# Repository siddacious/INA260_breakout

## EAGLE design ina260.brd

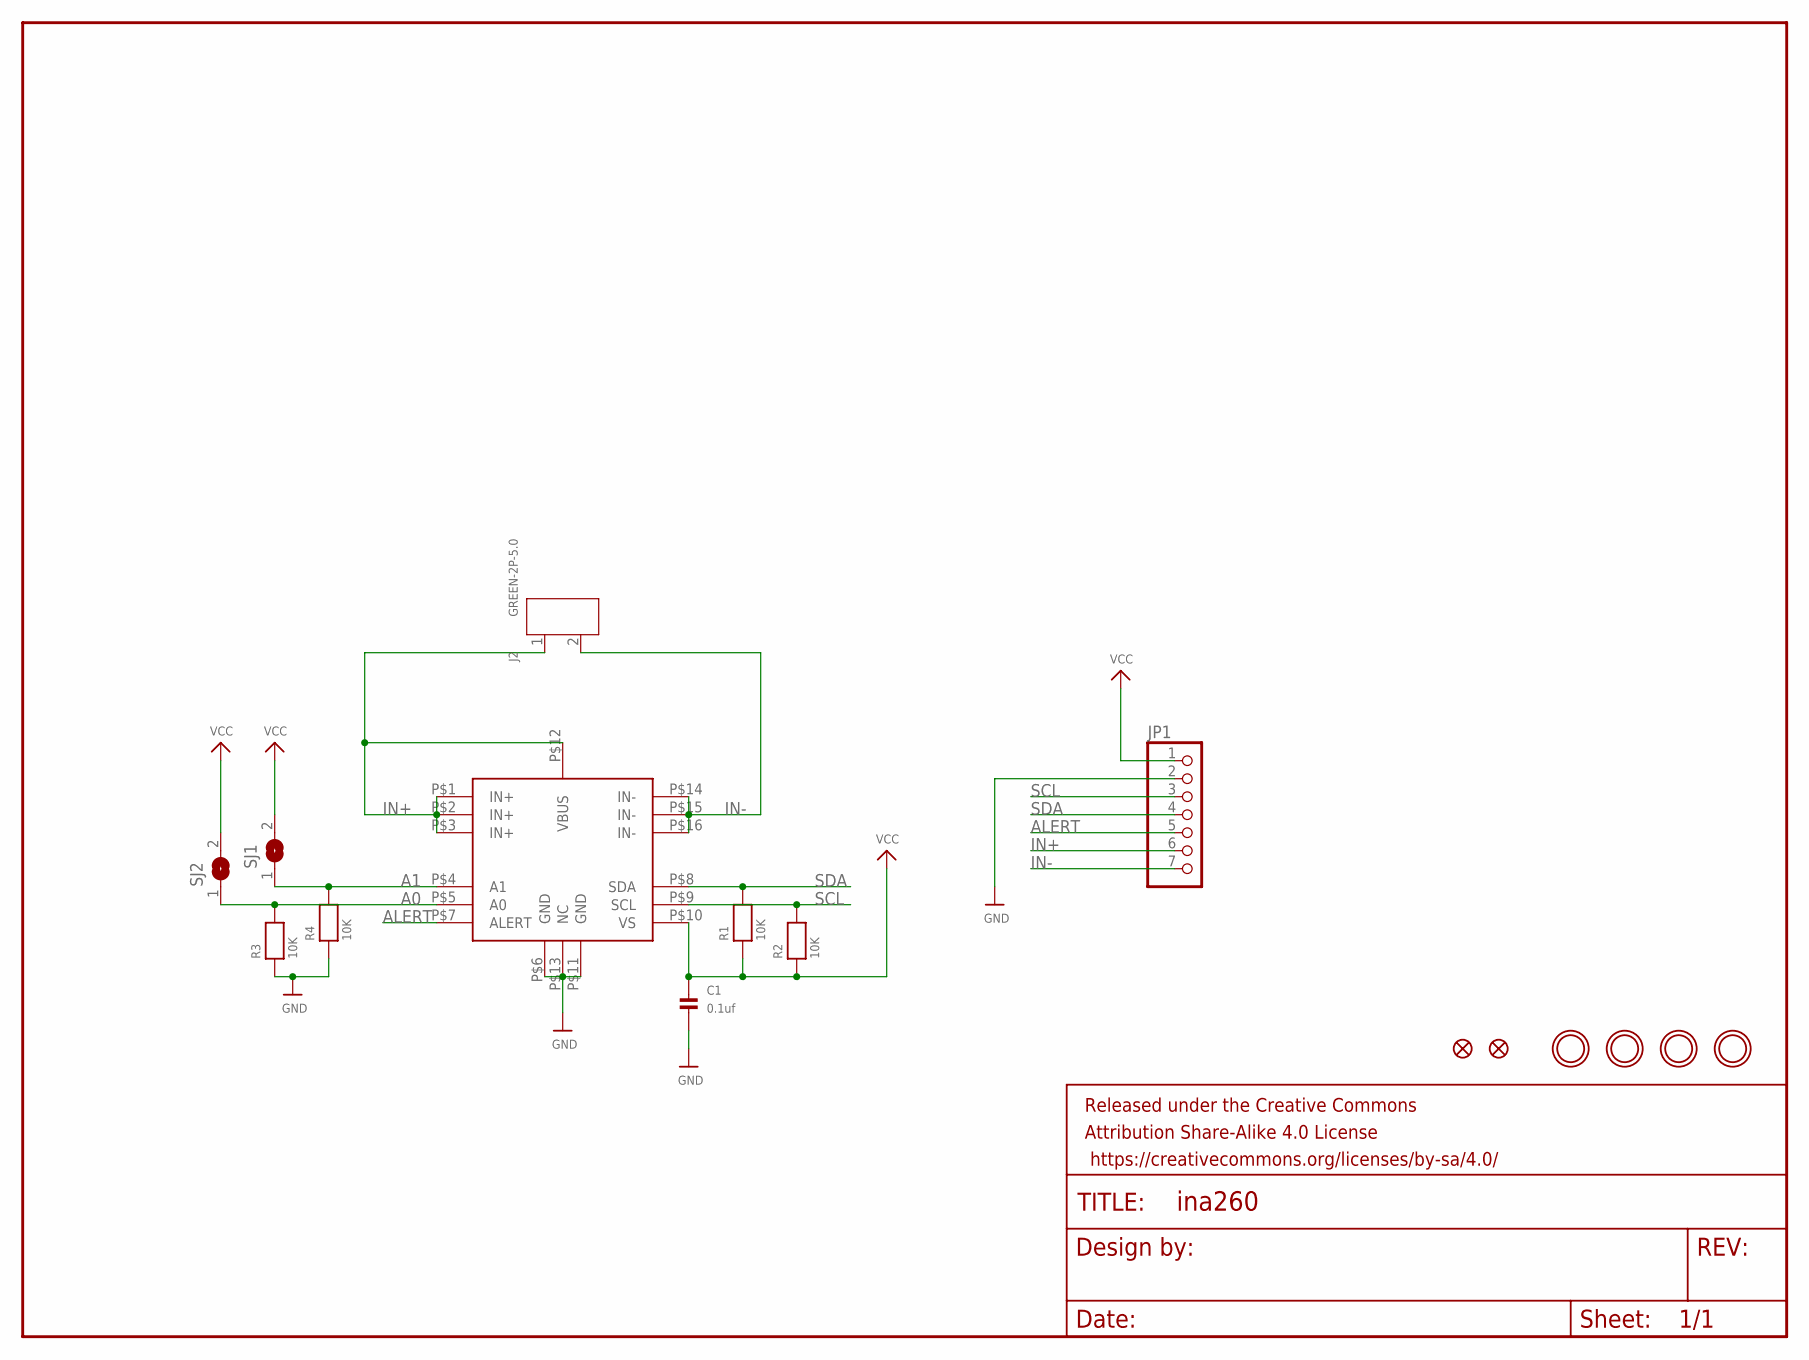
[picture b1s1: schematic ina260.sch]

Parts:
C1: 0.1uf; 0805
FID3, FID4: MICROBUILDER_FIDUCIAL""; MICROBUILDER_FIDUCIAL_1MM
FRAME1: FRAME-LETTER; CREATIVE_COMMONS
J2: GREEN-2P-5.0; H2-5.0-10.5X8.0MM
JP1: HEADER-1X7ROUND; 1X07_ROUND
R1, R2, R3, R4: 10K; 0805
SJ1, SJ2: SOLDERJUMPERREFLOW_NOPASTE; SOLDERJUMPER_REFLOW_NOPASTE
U$1: INA260; INA260_TSSOP16
U$5, U$6, U$7, U$8: MOUNTINGHOLE2.5; MOUNTINGHOLE_2.5_PLATED

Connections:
A0: R3.2, SJ2.1, U$1.P$5 (A0)
A1: R4.2, SJ1.1, U$1.P$4 (A1)
ALERT: JP1.5, U$1.P$7 (ALERT)
GND: C1.2, JP1.2, R3.1, R4.1, U$1.P$6 (GND), U$1.P$11 (GND), U$1.P$13 (NC)
IN+: J2.1, JP1.6, U$1.P$1 (IN+), U$1.P$2 (IN+), U$1.P$3 (IN+), U$1.P$12 (VBUS)
IN-: J2.2, JP1.7, U$1.P$14 (IN-), U$1.P$15 (IN-), U$1.P$16 (IN-)
SCL: JP1.3, R2.2, U$1.P$9 (SCL)
SDA: JP1.4, R1.2, U$1.P$8 (SDA)
VCC: C1.1, JP1.1, R1.1, R2.1, SJ1.2, SJ2.2, U$1.P$10 (VS)

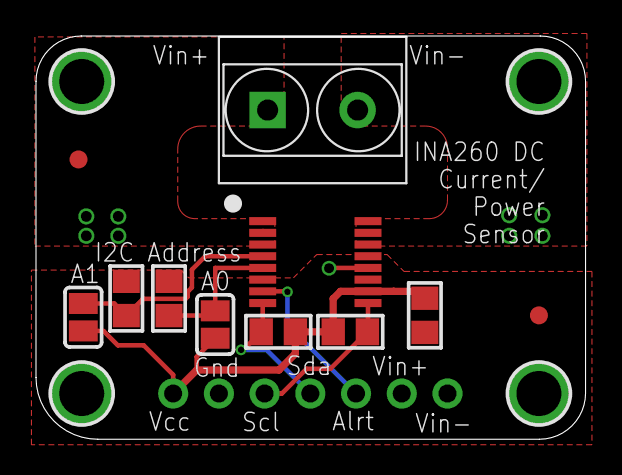
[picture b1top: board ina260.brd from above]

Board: 2 copper layers, 30.5 x 22.4 mm, 17 parts (0 on the bottom side), 9 nets.

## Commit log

2019-03-01 Initial working version, tweaked to fix text and fiducials, with basic test code

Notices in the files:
parts and their libraries:
SparkFun-Aesthetics: Licensing: Creative Commons ShareAlike 4.0 International - https://creativecommons.org/licenses/by-sa/4.0
SparkFun-Aesthetics: Released under the Creative Commons Attribution Share-Alike 4.0 License
SparkFun-Aesthetics: https://creativecommons.org/licenses/by-sa/4.0
